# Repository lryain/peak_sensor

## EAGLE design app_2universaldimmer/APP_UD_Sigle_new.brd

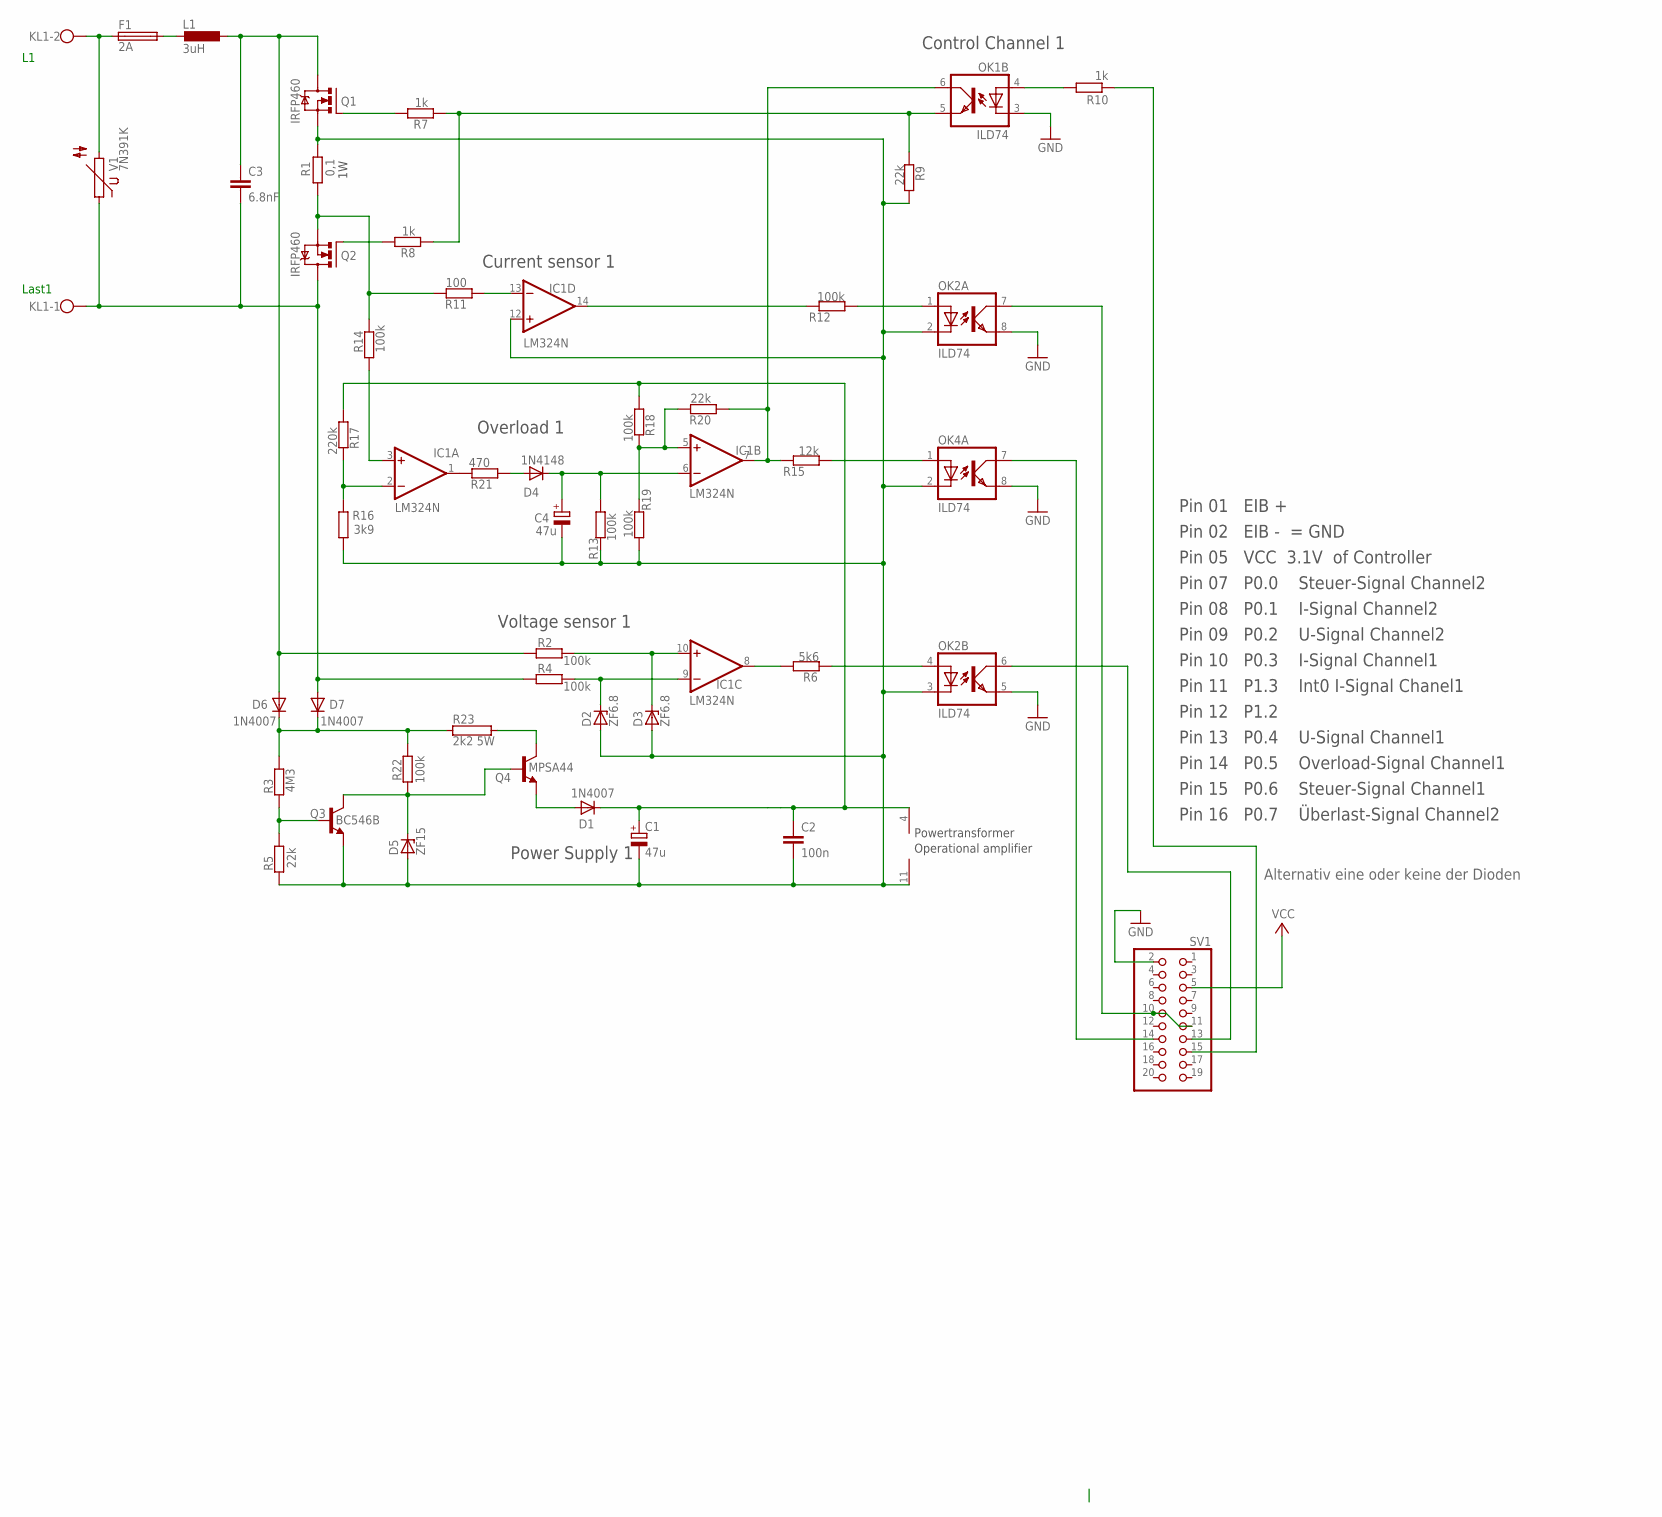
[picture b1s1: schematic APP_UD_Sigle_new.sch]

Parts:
C1, C4: 47u; E2-5
C2: 100n; C025-030X050
C3: 6.8nF; C050-075X075
D1: 1N4007; D-7
D2: ZF6.8; ZDIO-5
D3: ZF6.8; ZDIO-7.5
D4: 1N4148; D-7
D5: ZF15; ZDIO-7.5
D6, D7: 1N4007; D-7.5
F1: 2A; TR5
IC1: LM324N; DIL14
KL1: W237-102
L1: 3uH; 0414V
OK1, OK2, OK4: ILD74; DIL08
Q1, Q2: IRFP460; TO247BV
Q3: BC546B; TO92-EBC
Q4: MPSA44; TO92-EBC
R1: 0,1; 0414V
R2, R4, R12, R13, R14, R18, R19, R22: 100k; 0204/7
R3: 4M3; 0204/7
R5, R9, R20: 22k; 0204/7
R6: 5k6; 0204/7
R7, R8, R10: 1k; 0204/7
R11: 100; 0204/7
R15: 12k; 0204/7
R16: 3k9; 0204/7
R17: 220k; 0204/7
R21: 470; 0204/7
R23: 2k2 5W; KH208-8_10B
SV1: PINHD-2X10; 2X10
V1: 7N391K; S05K11

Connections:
AGND1: C1.-, C2.2, C4.-, D2.A, D3.A, D5.A, IC1.11 (V-), IC1.12 (+IN), OK2.2 (C), OK2.3 (C), OK4.2 (C), Q1.S, Q3.E, R1.2, R5.1, R9.2, R13.2, R16.2, R19.1
GND: OK1.3 (C), OK2.5 (EMIT), OK2.8 (EMIT), OK4.8 (EMIT), SV1.2
unnamed: R10.1, SV1.15
unnamed: OK1.4 (A), R10.2
unnamed: C3.1, D6.A, L1.1, Q1.D, R2.1
unnamed: Q2.S, R1.1, R11.2, R14.2
unnamed: OK2.6 (COL), SV1.13
unnamed: IC1.7 (OUT), OK1.6 (COL), R15.2, R20.1
unnamed: OK2.7 (COL), SV1.10, SV1.11
unnamed: F1.1, KL1.2, V1.2
unnamed: Q2.G, R8.2
unnamed: IC1.3 (+IN), R14.1
unnamed: D6.C, D7.C, R3.2, R22.2, R23.P$1 (1)
unnamed: OK2.4 (A), R6.1
unnamed: IC1.8 (OUT), R6.2
unnamed: Q3.B, R3.1, R5.2
unnamed: Q1.G, R7.2
unnamed: C3.2, D7.A, KL1.1, Q2.D, R4.1, V1.1
unnamed: IC1.2 (-IN), R16.1, R17.2
unnamed: F1.2, L1.2
unnamed: D3.C, IC1.10 (+IN), R2.2
unnamed: D2.C, IC1.9 (-IN), R4.2
unnamed: IC1.1 (OUT), R21.2
unnamed: OK2.1 (A), R12.1
unnamed: C4.+, D4.C, IC1.6 (-IN), R13.1
unnamed: D5.C, Q3.C, Q4.B, R22.1
unnamed: OK4.1 (A), R15.1
unnamed: OK4.7 (COL), SV1.14
unnamed: IC1.5 (+IN), R18.2, R19.2, R20.2
unnamed: Q4.C, R23.P$2 (2)
unnamed: D1.A, Q4.E
unnamed: IC1.14 (OUT), R12.2
unnamed: D4.A, R21.1
unnamed: OK1.5 (EMIT), R7.1, R8.1, R9.1
unnamed: IC1.13 (-IN), R11.1
V12-C1: C1.+, C2.1, D1.C, IC1.4 (V+), R17.1, R18.1
VCC: SV1.5

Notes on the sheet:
Voltage sensor 1
Power Supply 1
Control Channel 1
Pin 05 VCC 3.1V of Controller
Pin 02 EIB - = GND
Pin 01 EIB +
Pin 07 P0.0 Steuer-Signal Channel2
Pin 08 P0.1 I-Signal Channel2
Pin 09 P0.2 U-Signal Channel2
Pin 10 P0.3 I-Signal Channel1
Pin 13 P0.4 U-Signal Channel1
Pin 14 P0.5 Overload-Signal Channel1
Pin 15 P0.6 Steuer-Signal Channel1
Pin 16 P0.7 Überlast-Signal Channel2
Overload 1
Last1
Powertransformer
Operational amplifier
Current sensor 1
Pin 11 P1.3 Int0 I-Signal Chanel1
Pin 12 P1.2
Alternativ eine oder keine der Dioden

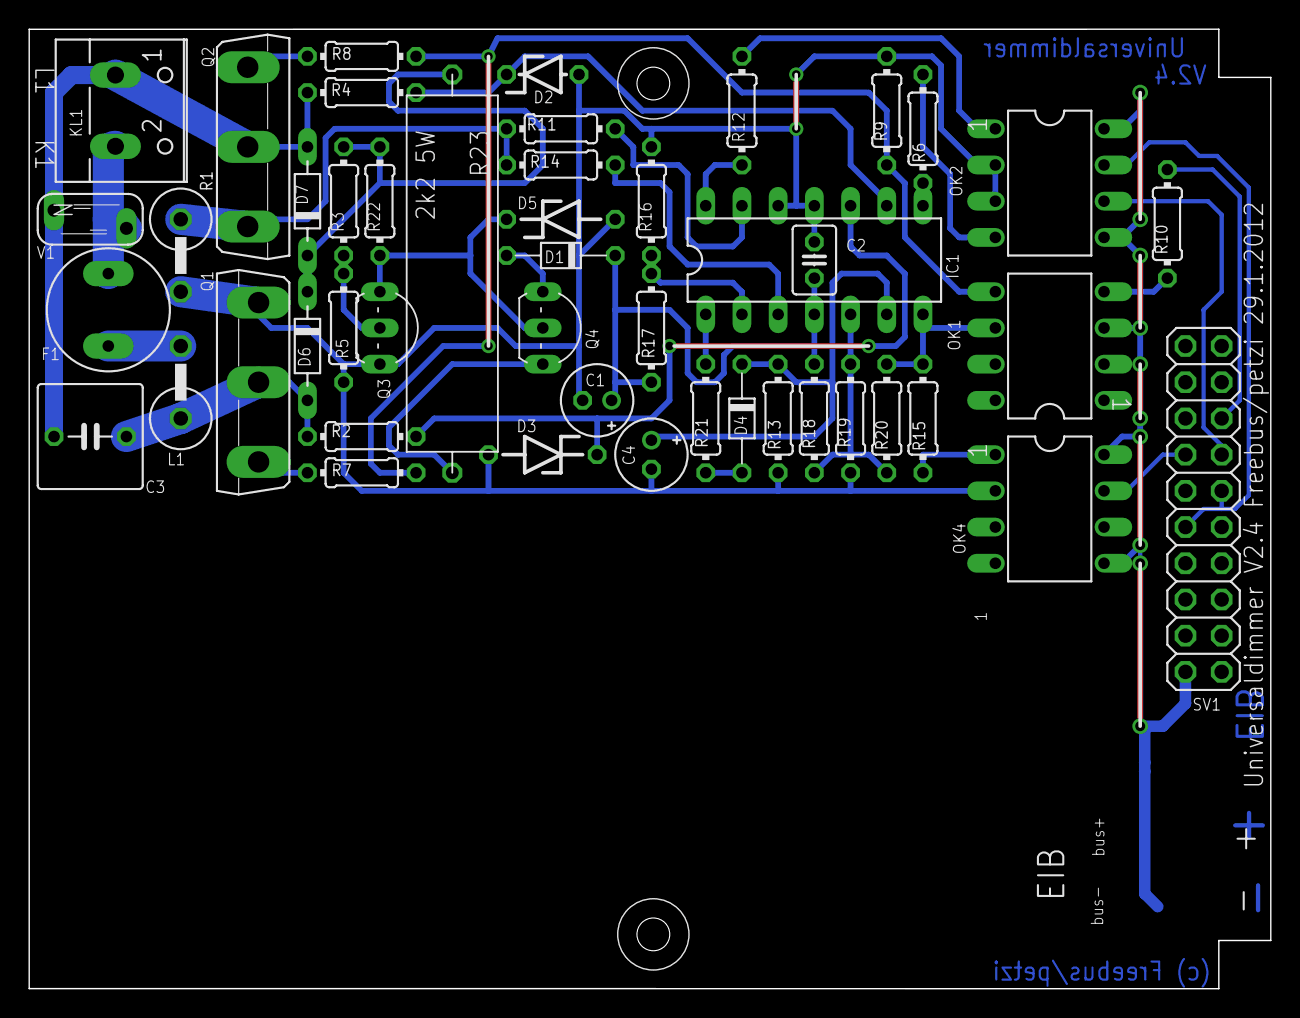
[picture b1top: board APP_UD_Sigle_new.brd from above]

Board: 2 copper layers, 87.1 x 67.3 mm, 47 parts (0 on the bottom side), 36 nets.

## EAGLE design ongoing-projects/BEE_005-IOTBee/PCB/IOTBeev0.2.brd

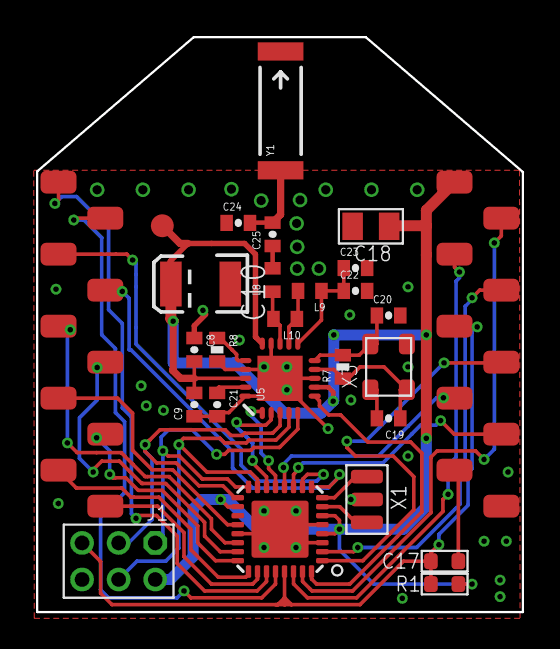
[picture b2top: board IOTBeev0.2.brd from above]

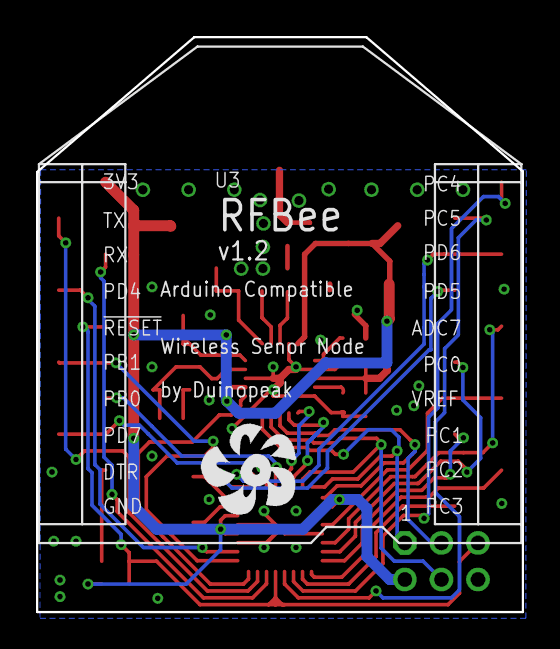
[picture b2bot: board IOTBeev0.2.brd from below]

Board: 2 copper layers, 27.0 x 31.9 mm, 27 parts (2 on the bottom side), 37 nets.

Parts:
C8: 10nF; 0402-CAP
C9: 1nF; 0402-CAP
C10: 10uF; EIA3528
C17: 100nF; 0603_S
C18: 10u; 0805
C19, C20: 22pF; 0402-CAP
C21: 33nF; 0402-CAP
C22: 2.2nF; 0402-CAP
C23: 4.7pF; 0402-CAP
C24: 1.0pF; 0402-CAP
C25: 1.5pF; 0402-CAP
J1: CK_2X3_2.0
L8: 3.9nH; C0402
L9: 2.7nH; C0402
L10: 8.2nH; C0402
R1: 10k; 0603_S
R7: 1M; 0402-RES
R8: 22K; 0402-RES
TP1: PAD.03X.05
U1: MEGA8; MLF32X
U3: 20P-SMD-2.0-BT
U5: NRF24L01ALT1; QFN20_ALT1
U$1: DUINOFUN-LOGO-PCB-0.7
X1: 16MHz; XTAL_3X2
X3: 26MHz; X3225
Y1: ANTENNA2SMD5; ANTENNA-CHIP5

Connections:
!RESET: C17.2, J1.3, R1.2, U1.29, U3.5
+3V3: C8.2, C9.2, C10.A, C18.1, J1.6, R1.1, TP1.P$1, U1.4, U1.6, U1.18, U3.1, U5.7, U5.15, U5.18
ADC7: U1.22, U3.16
ANT: C24.2, C25.2, Y1.FEED
AREF: U1.20, U3.14
CE: U1.13, U5.1
CSN: U1.14, U5.2
DTR: C17.1, U3.9
GND: C8.1, C9.1, C10.C, C18.2, C19.2, C20.2, C21.2, C22.2, C23.2, C24.1, J1.4, R8.2, U1.3, U1.5, U1.21, U1.HEAT, U3.10, U5.0, U5.8, U5.14, U5.17, U5.20, X1.2, X3.1, X3.3
IRQ: U1.32, U5.6
MISO: J1.1, U1.16, U5.5
MOSI: J1.5, U1.15, U5.4
unnamed: U1.7, X1.1
unnamed: U1.8, X1.3
unnamed: C19.1, R7.1, U5.9, X3.2
unnamed: C20.1, R7.2, U5.10, X3.4
unnamed: L8.1, L10.2, U5.13
unnamed: C22.1, C23.1, L9.1, U5.11
unnamed: R8.1, U5.16
unnamed: C21.1, U5.19
unnamed: L9.2, L10.1, U5.12
unnamed: C25.1, L8.2
PB0: U1.12, U3.7
PC0: U1.23, U3.15
PC1: U1.24, U3.13
PC2: U1.25, U3.12
PC3: U1.26, U3.11
PD3: U1.1, U3.6
PD4: U1.2, U3.4
PD5: U1.9, U3.17
PD6: U1.10, U3.18
PD7: U1.11, U3.8
RX: U1.30, U3.3
SCK: J1.2, U1.17, U5.3
SCL: U1.28, U3.19
SDA: U1.27, U3.20
TX: U1.31, U3.2

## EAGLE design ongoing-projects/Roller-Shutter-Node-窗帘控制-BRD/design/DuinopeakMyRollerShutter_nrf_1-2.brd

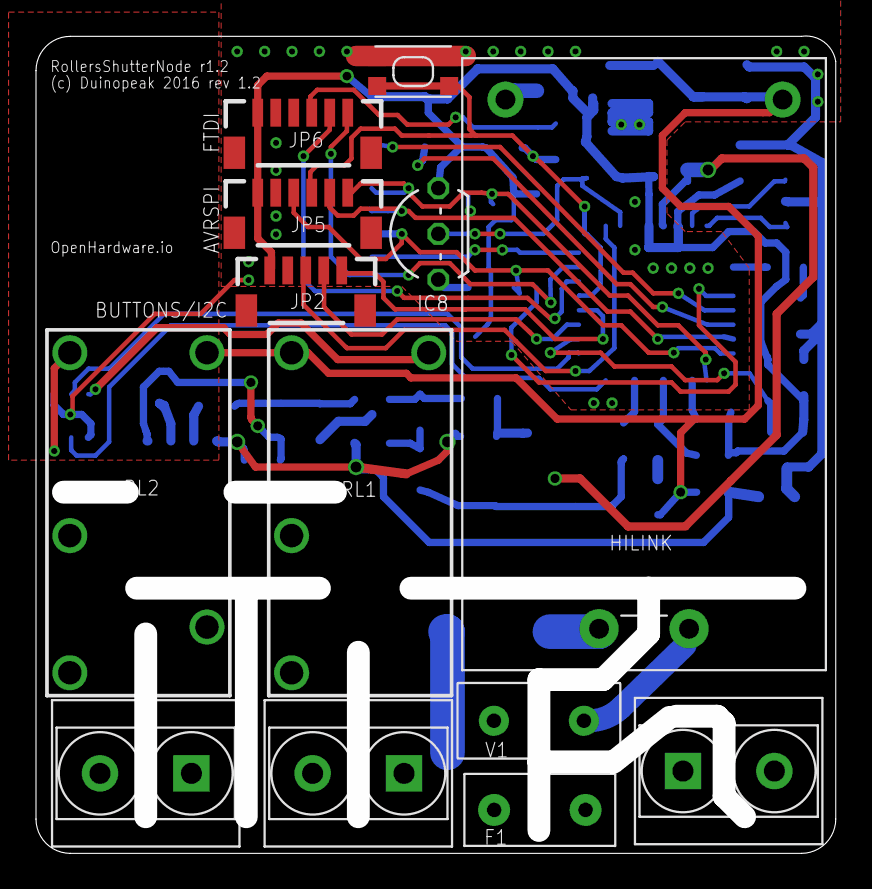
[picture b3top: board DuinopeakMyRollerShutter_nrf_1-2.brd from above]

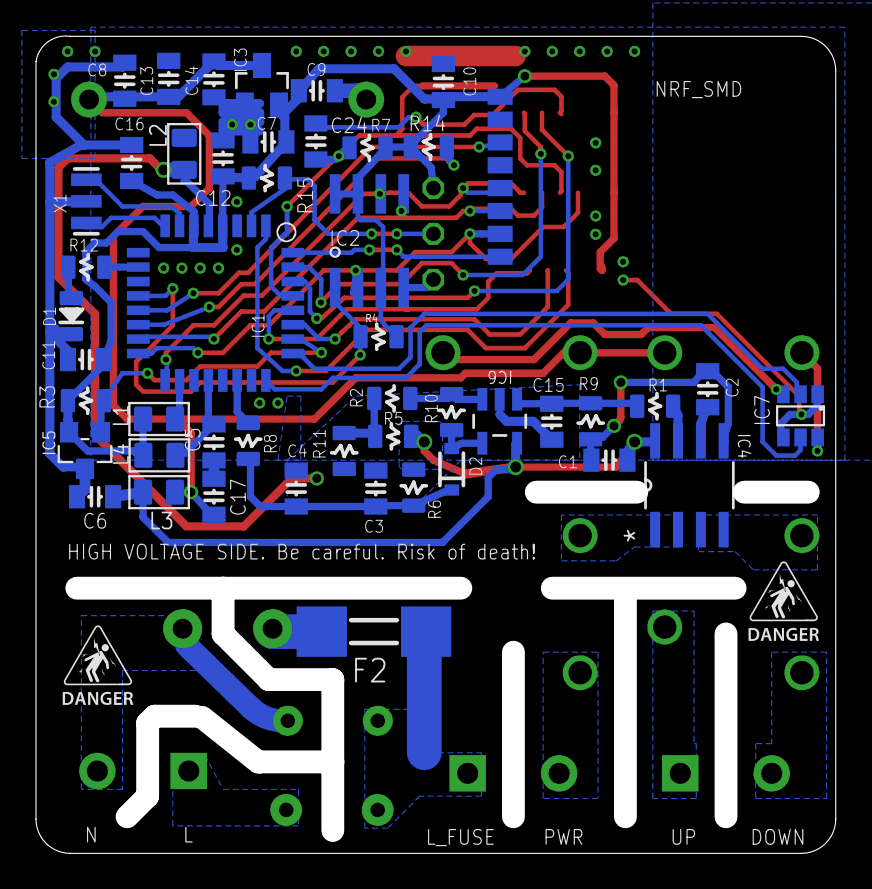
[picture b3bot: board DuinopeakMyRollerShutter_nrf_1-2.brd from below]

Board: 2 copper layers, 44.4 x 45.4 mm, 63 parts (50 on the bottom side), 48 nets.

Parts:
C1: 0.1uf; 0805-CAP
C2, C6, C17: 10n; 0805-CAP
C3, C10, C13: 4u7; 0805-CAP
C4, C5, C7, C11, C12, C14, C16: 0.1u; 0805-CAP
C8: 1u; 0805-CAP
C9: 10u; 0805-CAP
C15: DNP; 0805-CAP
C24: 100n; 0805-CAP
D1: LED0805; 0805-LED
D2: 1n916 type..; SOD-323
F1: FUSE_BEL_RST5_5A
F2: FUSE_MF2410; 2410
HILINK: HILINK_HLK-PM01
IC1: ATMega-328; TQFP32-08
IC2: AT25DF512C-SSHN-B; SO-08
IC3: MCP1703CB; SOT23
IC4: ACS712_5A; SOIC127P600X175-8N
IC5: ATSHA204A; SOT23
IC6: LM321; SOT95P285X120-5N
IC7: MDC3105DMT1
IC8: DS1820; TO92-
J1, J2, J3: SCREW-TERMINAL-2P-3470110P1; 2P-5.0
JP2: 1X05-1MM
JP5, JP6: 1X06-1MM
L1, L2, L3, L4: or 0ohms; L0805
NRF_SMD: NRF24L01+SMD_MODULE
R1, R2, R7, R8, R9, R15: 10k; 0805-RES
R3, R14: 56k; 0805-RES
R4: 0805-RES
R5: 4.7k; 0805-RES
R6: 100k; 0805-RES
R10: 47k; 0805-RES
R11: 2k; 0805-RES
R12: 1k5; 0805-RES
RL1: G5Q-1A-5VDC; G5Q_SINGLE
RL2: G5Q-1-EU-5VDC; RELAY-G5Q
SW1: SPST_TACT-KMR2; KMR2
U$2, U$3: ELECTROCUTION_SMALL
V1: VARISTOR_B72207S251K101
X1: 8 MHz; RESONATOR-SMD

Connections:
5V: C8.1, C13.1, C14.1, C17.1, HILINK.V+, IC3.3, L4.2, RL1.1, RL2.5
12_220: J1.2, RL1.3
A3: IC1.26, IC5.1, R3.1
A4_SDA: IC1.27, JP2.2
A5_SCL: IC1.28, JP2.1
A6_ADC: C3.1, C4.2, D2.1, R6.2, R8.2
A7: IC1.22, R8.1
AGND: C1.2, C2.2, C3.2, C4.1, C15.2, IC1.5, IC4.5, IC6.2, L2.2, R6.1, R9.1, R11.1
AREF: C5.1, IC1.20, L3.1
D0_RX: IC1.30, JP6.5
D1_TX: IC1.31, JP6.6
D2: IC1.32, NRF_SMD.IRQ
D3: IC1.1, JP2.3
D4: IC1.2, IC8.2, R15.2
D9: IC1.13, NRF_SMD.CE
DTR: C24.1, JP6.4
FLASH_CSN: IC1.12, IC2.1, R4.1
GND: C5.2, C6.2, C7.2, C8.2, C9.2, C10.1, C11.2, C12.2, C13.2, C14.2, C16.2, C17.2, D1.MINUS, HILINK.V-, IC1.3, IC1.21, IC2.4, IC3.1, IC5.3, IC7.GND1, IC7.GND2, IC8.1, JP2.4, JP5.2, JP6.2, JP6.3, L2.1, NRF_SMD.GND, SW1.1, SW1.3, X1.2
IN_ACS: IC4.1, IC4.2, RL1.2
L: F1.1, J2.1
LED: IC1.10, R12.1
LM_OUT: D2.2, IC6.4, R10.2
MISO: IC1.16, IC2.2, JP5.3, NRF_SMD.MISO
MOSI: IC1.15, IC2.5, JP5.5, NRF_SMD.MOSI
M_DOWN: J3.2, RL2.3
M_UP: J3.1, RL2.4
N: HILINK.AC2, J2.2, V1.1
unnamed: C2.1, IC4.6
unnamed: IC4.7, R1.1
unnamed: IC1.18, L1.2
unnamed: IC7.VOUT2, RL1.5
unnamed: F2.2, HILINK.AC1
unnamed: C15.1, IC6.1, R1.2, R9.2
unnamed: IC6.3, R2.1, R10.1
unnamed: IC1.7, X1.1
unnamed: D1.PLUS, R12.2
unnamed: R2.2, R5.1, R11.2
unnamed: IC7.VOUT1, RL2.1
unnamed: IC1.8, X1.3
OUT_ACS: IC4.3, IC4.4, RL2.2
PHASE: F1.2, F2.1, J1.1, V1.2
REL_DOWN: IC1.25, IC7.VIN2
REL_UP: IC1.24, IC7.VIN1
RF_CSN: IC1.14, R14.1
RST: C24.2, IC1.29, JP5.4, R7.2, SW1.2, SW1.4
SCK: IC1.17, IC2.6, JP5.6, NRF_SMD.SCK
VCC: C7.1, C9.1, C10.2, C11.1, C12.1, C16.1, IC1.4, IC1.6, IC2.3, IC2.7, IC2.8, IC3.2, IC5.2, IC8.3, JP2.5, JP5.1, JP6.1, L1.1, L3.2, NRF_SMD.3V, R3.2, R4.2, R7.1, R14.2, R15.1
VCC_ACS: C1.1, C6.1, IC4.8, IC6.5, L4.1, R5.2

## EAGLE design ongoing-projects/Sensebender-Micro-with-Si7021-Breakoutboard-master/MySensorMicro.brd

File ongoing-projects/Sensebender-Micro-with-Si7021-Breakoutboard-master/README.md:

# Sensebender-Micro-with-Si7021-Breakoutboard
Clone of the <a href="https://github.com/mysensors/SensebenderMicro">original SenseBender Micro Board</a> but using the Si7021 on a breakout board.

This repository contains a clone of the original Sensebender Micro board from  -> <a href="http://www.mysensors.org">Mysensors</a>

As I find it hard to solder the used Si7021 I decided to exchange it with a breakout variant. Those are available for actually less money than the chip itself on Aliexpress or ebay. Just search for Si7021.

However - as I'm a totally newbie to Eagle, this is a work in progress. So be aware that it is not finished yet and needs some testing. :)

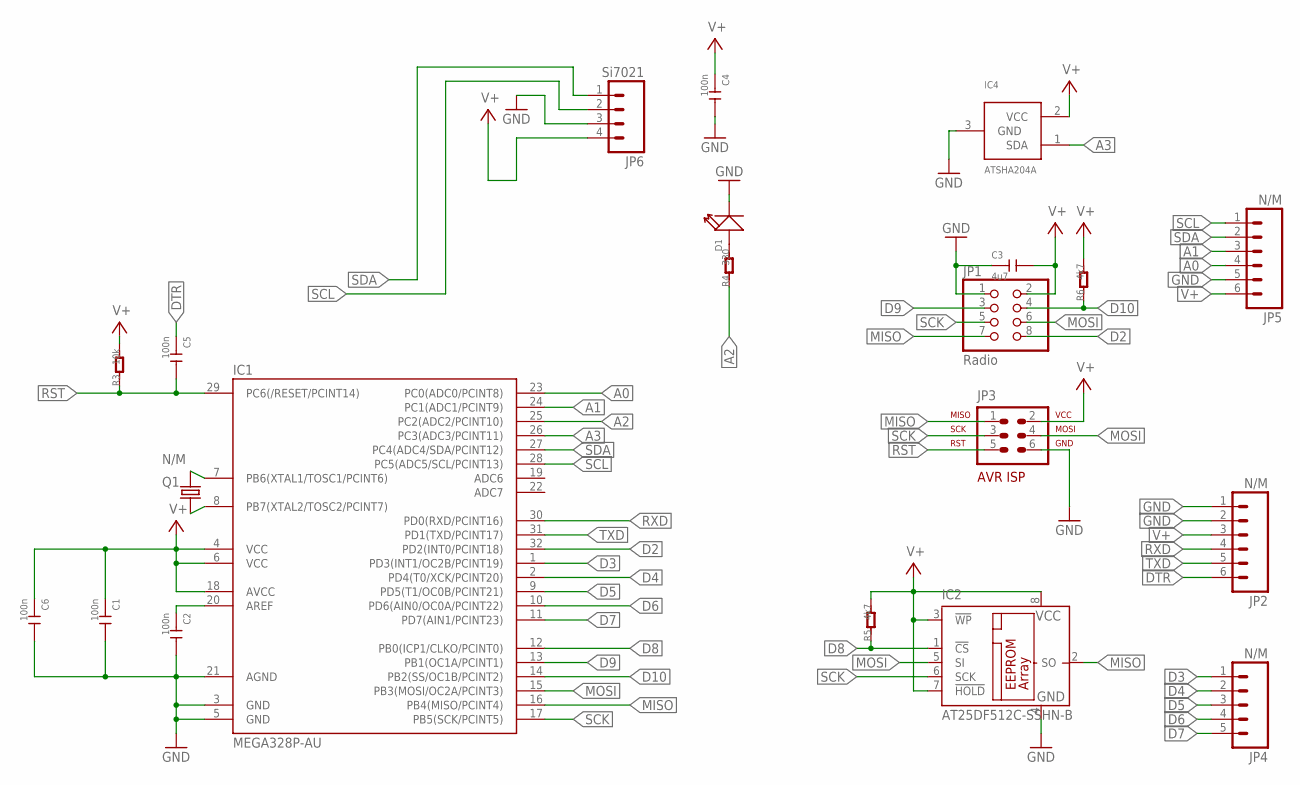
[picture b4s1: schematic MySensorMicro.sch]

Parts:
C1, C2, C4, C5, C6: 100n; C0402
C3: 4u7; C0603
D1: LED-0402
IC1: MEGA328P-AU; TQFP32-08
IC2: AT25DF512C-SSHN-B; SO-08
IC4: ATSHA204A; SOT23
JP1: Radio; 2X04
JP2, JP5: N/M; 1X06_NO_SILK
JP3: N/M; AVR-ISP-6
JP4: N/M; 1X05_NO_SILK
JP6: Si7021; 1X04
Q1: N/M; 2P-L3.2XW1.5MM
R3: 10k; R0402
R4: 330; R0402
R5, R6: 4k7; R0402

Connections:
A0: IC1.23 (PC0(ADC0/PCINT8)), JP5.4
A1: IC1.24 (PC1(ADC1/PCINT9)), JP5.3
A2: IC1.25 (PC2(ADC2/PCINT10)), R4.1
A3: IC1.26 (PC3(ADC3/PCINT11)), IC4.1 (SDA)
D2: IC1.32 (PD2(INT0/PCINT18)), JP1.8
D3: IC1.1 (PD3(INT1/OC2B/PCINT19)), JP4.1
D4: IC1.2 (PD4(T0/XCK/PCINT20)), JP4.2
D5: IC1.9 (PD5(T1/OC0B/PCINT21)), JP4.3
D6: IC1.10 (PD6(AIN0/OC0A/PCINT22)), JP4.4
D7: IC1.11 (PD7(AIN1/PCINT23)), JP4.5
D8: IC1.12 (PB0(ICP1/CLKO/PCINT0)), IC2.1 (!CS), R5.1
D9: IC1.13 (PB1(OC1A/PCINT1)), JP1.3
D10: IC1.14 (PB2(SS/OC1B/PCINT2)), JP1.4, R6.1
DTR: C5.1, JP2.6
GND: C1.2, C2.2, C3.1, C4.2, C6.2, D1.-, IC1.3 (GND), IC1.5 (GND), IC1.21 (AGND), IC2.4 (GND), IC4.3 (GND), JP1.1, JP2.1, JP2.2, JP3.6, JP5.5, JP6.3
MISO: IC1.16 (PB4(MISO/PCINT4)), IC2.2 (SO), JP1.7, JP3.1
MOSI: IC1.15 (PB3(MOSI/OC2A/PCINT3)), IC2.5 (SI), JP1.6, JP3.4
unnamed: IC1.7 (PB6(XTAL1/TOSC1/PCINT6)), Q1.1
unnamed: IC1.8 (PB7(XTAL2/TOSC2/PCINT7)), Q1.2
unnamed: D1.+, R4.2
unnamed: C2.1, IC1.20 (AREF)
RST: C5.2, IC1.29 (PC6(/RESET/PCINT14)), JP3.5, R3.1
RXD: IC1.30 (PD0(RXD/PCINT16)), JP2.4
SCK: IC1.17 (PB5(SCK/PCINT5)), IC2.6 (SCK), JP1.5, JP3.3
SCL: IC1.28 (PC5(ADC5/SCL/PCINT13)), JP5.1, JP6.2
SDA: IC1.27 (PC4(ADC4/SDA/PCINT12)), JP5.2, JP6.1
TXD: IC1.31 (PD1(TXD/PCINT17)), JP2.5
V+: C1.1, C3.2, C4.1, C6.1, IC1.4 (VCC), IC1.6 (VCC), IC1.18 (AVCC), IC2.3 (!WP), IC2.7 (!HOLD), IC2.8 (VCC), IC4.2 (VCC), JP1.2, JP2.3, JP3.2, JP5.6, JP6.4, R3.2, R5.2, R6.2

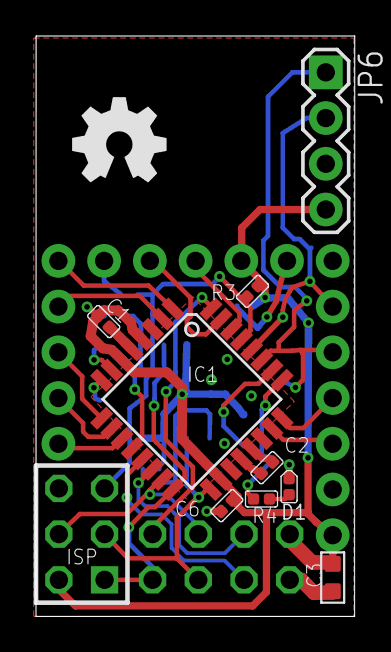
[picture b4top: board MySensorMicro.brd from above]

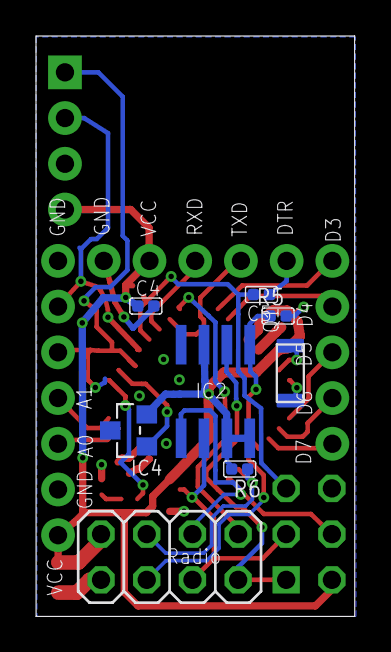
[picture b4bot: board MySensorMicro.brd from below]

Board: 2 copper layers, 17.7 x 32.2 mm, 21 parts (8 on the bottom side), 28 nets.

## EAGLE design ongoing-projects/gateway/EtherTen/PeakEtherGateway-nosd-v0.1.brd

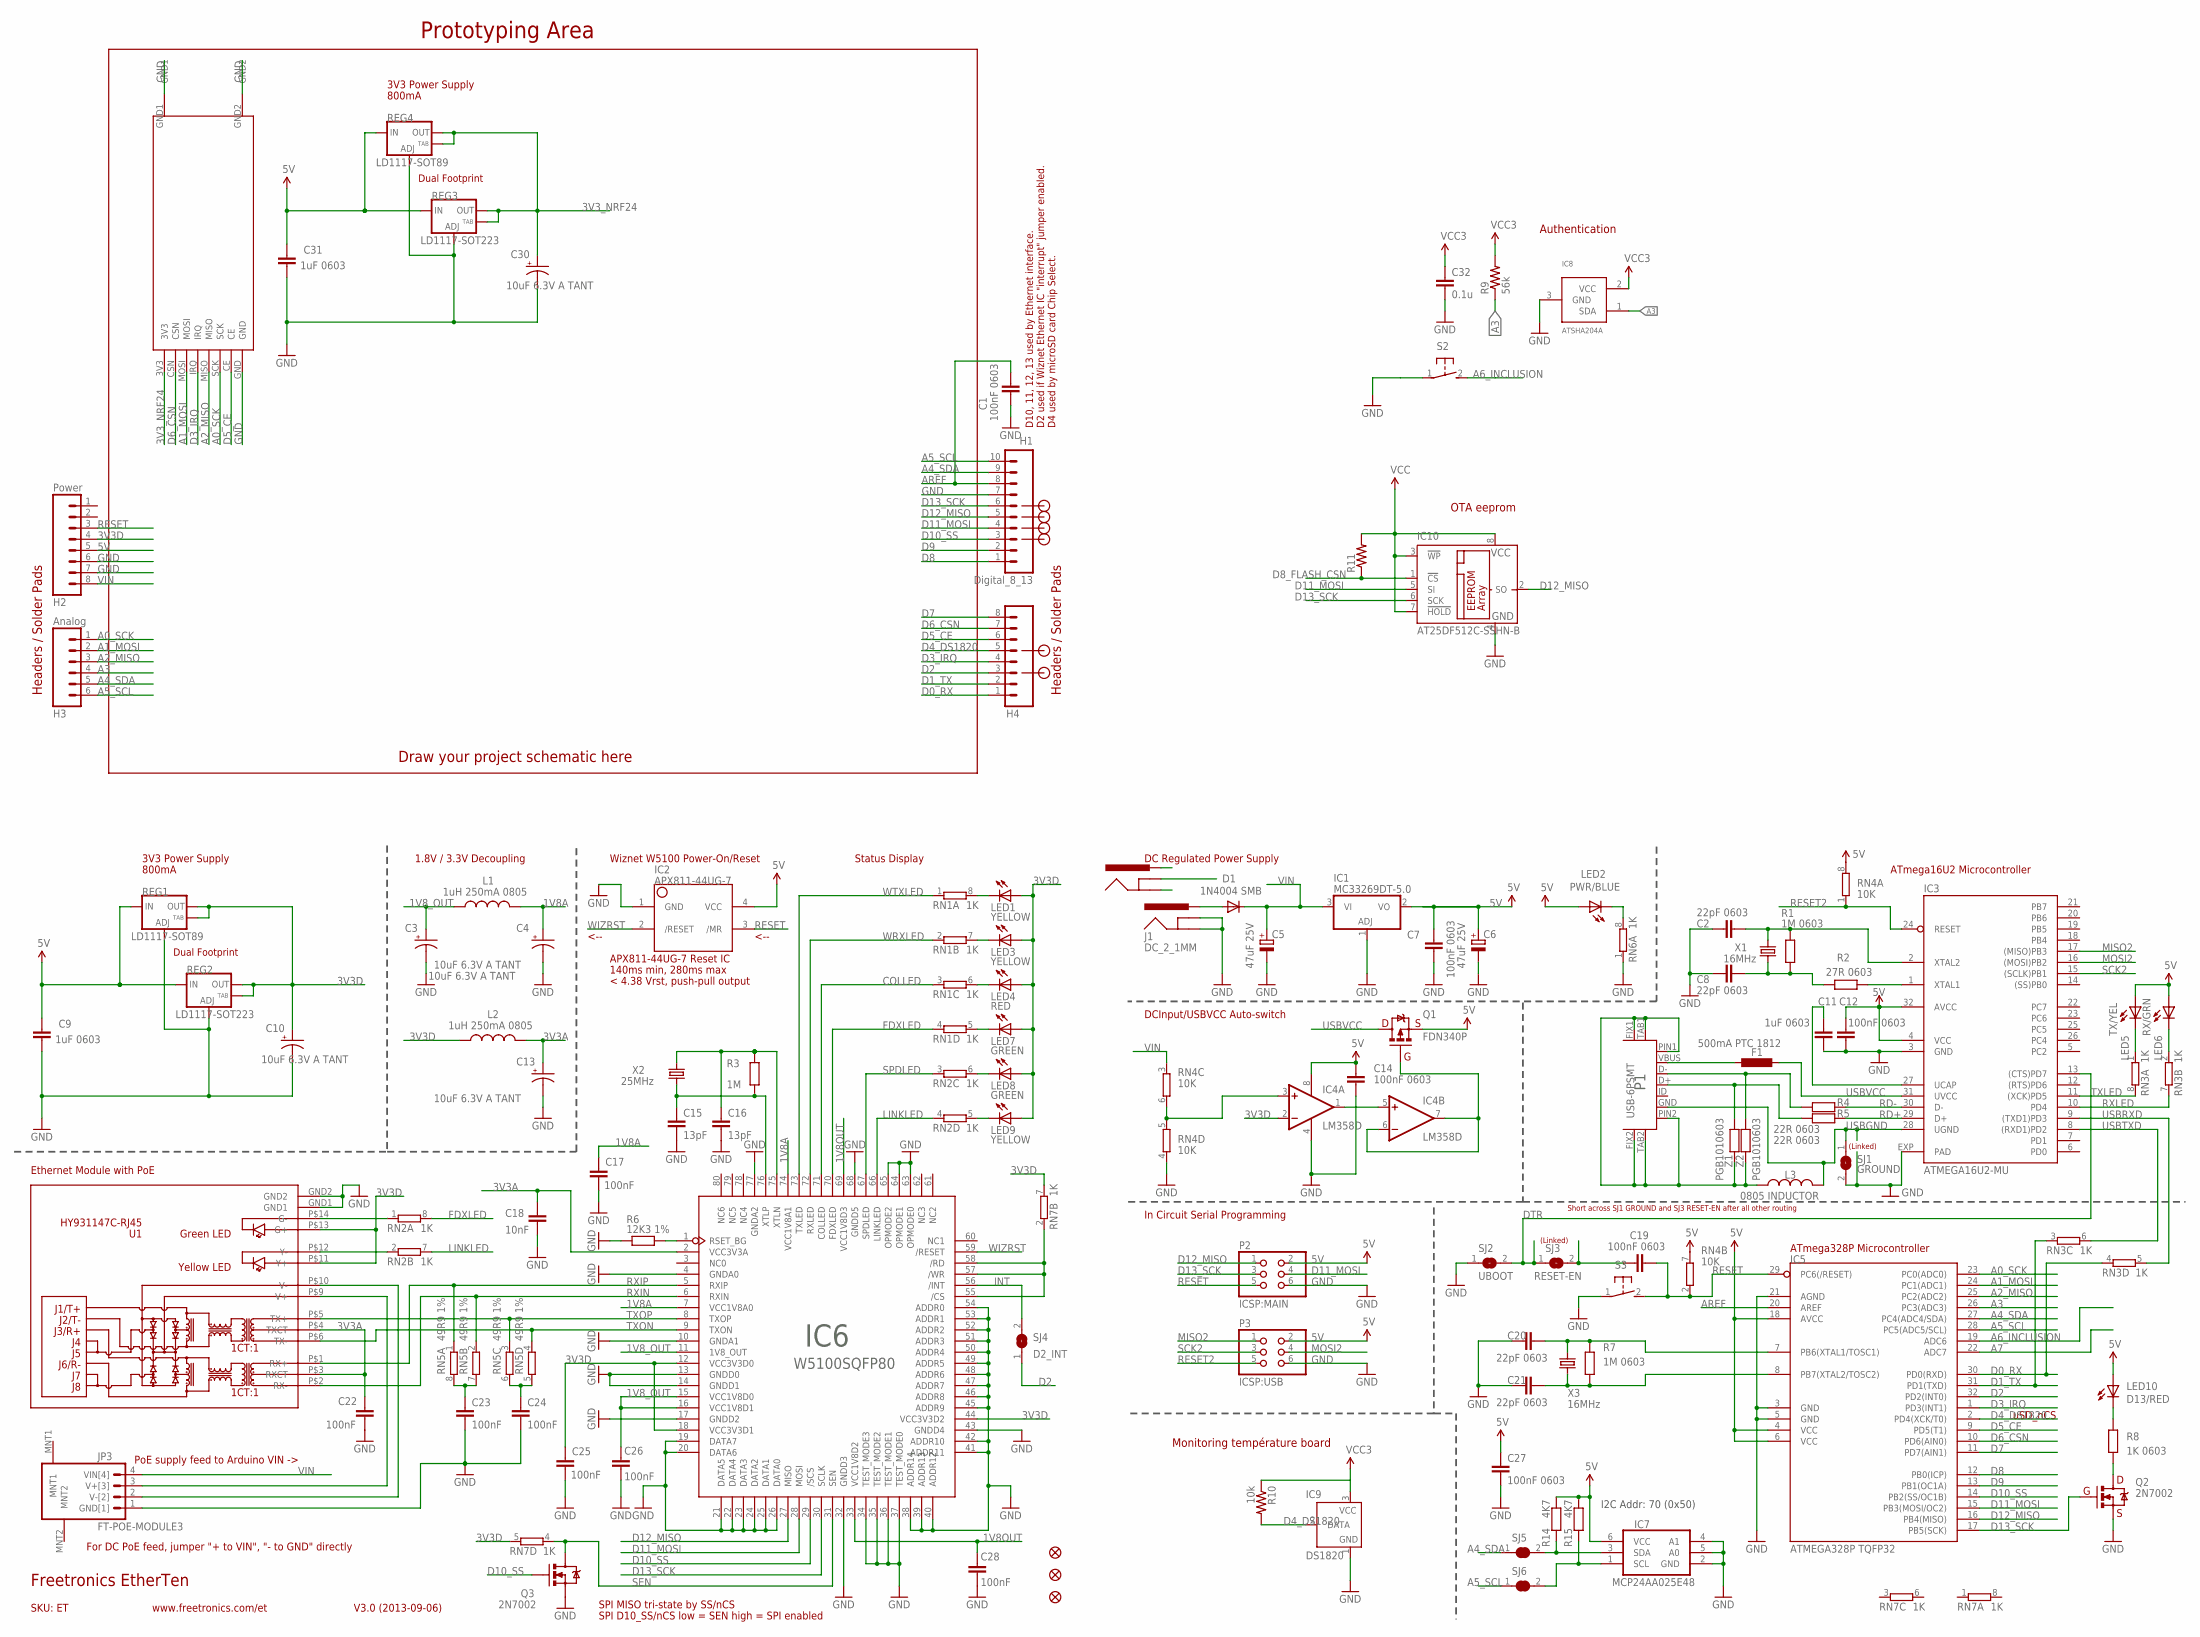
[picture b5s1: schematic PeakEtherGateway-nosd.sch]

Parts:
C1, C7, C12, C14, C19, C27: 100nF 0603; 0603
C2, C8, C20, C21: 22pF 0603; 0603
C3, C4, C10, C13, C30: 10uF 6.3V A TANT; EIA3216
C5, C6: 47uF 25V; PANASONIC_D
C9, C11, C31: 1uF 0603; 0603
C15, C16: 13pF; 0603
C17, C22, C23, C24, C25, C26, C28: 100nF; 0603
C18: 10nF; 0603
C32: 0.1u; 0603-CAP
D1: 1N4004 SMB; SMB-DIODE
F1: 500mA PTC 1812; L1812
FID1, FID2, FID3: FIDUCIAL1X2.5; FIDUCIAL-1X2.5
H1: Digital_8_13; 1X10
H2: Power; 1X08
H3: Analog; 1X06
H4: Digital_0_7; 1X08
IC1: MC33269DT-5.0; DPACK
IC2: APX811-44UG-7; SOT143-R
IC3: ATMEGA16U2-MU; ATMEL_QFN32
IC4: LM358D; SO08
IC5: ATMEGA328P TQFP32; TQFP32-08
IC6: W5100SQFP80; SQFP80
IC7: MCP24AA025E48; SOT23-6
IC8: ATSHA204A; SOT23
IC9: DS1820; TO92-
IC10: AT25DF512C-SSHN-B; SO-08
J1: DC_2_1MM; POWER_JACK_PTH
J2: POWER_JACKOVERPASTE_REDBOARD_0603; POWER_JACK_SMD_OVERPASTE_REDBOARD_0603
JP3: FT-POE-MODULE3; FT-POE-MODULE-NOLABEL
L1, L2: 1uH 250mA 0805; L2012C
L3: 0805 INDUCTOR; 0805-LARGE
LED1, LED3, LED9: YELLOW; LED-0603
LED2: PWR/BLUE; LED-0603
LED4: RED; LED-0603
LED5: TX/YEL; LED-0603
LED6: RX/GRN; LED-0603
LED7, LED8: GREEN; LED-0603
LED10: D13/RED; LED-0603
P1: USB-6PSMT; USB-MICROB-MB05PMXX
P2: ICSP:MAIN; 2X03
P3: ICSP:USB; 2X03
Q1: FDN340P; SOT23
Q2, Q3: 2N7002; SOT23-3
R1, R7: 1M 0603; 0603
R2: 27R 0603; 0603
R3: 1M; 0603
R4, R5: 22R 0603; 0603
R6: 12K3 1%; 0603
R8: 1K 0603; 0603
R9: 56k; 0603-RES
R10: 10k; 0603-RES
R11: RESISTOR0603-RES; 0603-RES
R14, R15: 4K7; 0603
REG1, REG4: LD1117-SOT89; SOT89
REG2, REG3: LD1117-SOT223; SOT223
RN1, RN2, RN3, RN6, RN7: 1K; CAY16
RN4: 10K; CAY16
RN5: 49R9 1%; CAY16
S2, S3: 31-XX; B3F-31XX
SJ1: GROUND; SJ
SJ2: UBOOT; SJ
SJ3: RESET-EN; SJ
SJ4: D2_INT; SJ
SJ5, SJ6: SJCN; SJC
U1: HY931147C-RJ45; HY931147C
U$17: NRF2401; NRF2401_PA_OUTLINE
X1, X3: 16MHz; HC49U-V
X2: 25MHz; HC49U-V
Z1, Z2: PGB1010603; 0603

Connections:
1V8A: C4.A (+), C17.1, IC6.7 (VCC1V8A0), IC6.74 (VCC1V8A1), L1.2
1V8OUT: C28.1, IC6.33 (VCC1V8D2), IC6.69 (VCC1V8D3)
1V8_OUT: C3.A (+), C26.1, IC6.11 (1V8_OUT), IC6.15 (VCC1V8D0), IC6.16 (VCC1V8D1), L1.1
3V3A: C13.A (+), C18.1, C22.1, IC6.2 (VCC3V3A), L2.2, U1.P$3 (RXCT), U1.P$4 (TXCT)
3V3D: C10.A (+), C25.1, H2.4, IC4.2 (-IN), IC6.12 (VCC3V3D0), IC6.18 (VCC3V3D1), IC6.44 (VCC3V3D2), L2.1, LED1.A, LED3.A, LED4.A, LED7.A, LED8.A, LED9.A, REG1.2 (OUT), REG1.4 (OUT), REG2.2 (OUT), REG2.4 (OUT), RN7.5 (2), RN7.7 (2), U1.P$11 (Y+), U1.P$13 (G+)
3V3_NRF24: C30.A (+), C32.1, IC8.2 (VCC), IC9.3 (VCC), IC10.3 (!WP), IC10.7 (!HOLD), IC10.8 (VCC), R9.2, R10.1, R11.2, REG3.2 (OUT), REG3.4 (OUT), REG4.2 (OUT), REG4.4 (OUT), U$17.3V3
5V: C6.+, C7.1, C9.1, C12.1, C14.1, C27.1, C31.1, H2.5, IC1.2 (VO), IC2.4 (VCC), IC3.4 (VCC), IC3.32 (AVCC), IC4.8 (V+), IC5.4 (VCC), IC5.6 (VCC), IC5.18 (AVCC), IC7.6 (VCC), LED2.A, LED5.A, LED6.A, LED10.A, P2.2, P3.2, Q1.2 (S), R14.1, R15.1, REG1.3 (IN), REG2.3 (IN), REG3.3 (IN), REG4.3 (IN), RN4.7 (2), RN4.8 (2)
A0_SCK: H3.1, IC5.23 (PC0(ADC0)), U$17.SCK
A1_MOSI: H3.2, IC5.24 (PC1(ADC1)), U$17.MOSI
A2_MISO: H3.3, IC5.25 (PC2(ADC2)), U$17.MISO
A3: H3.4, IC5.26 (PC3(ADC3)), IC8.1 (SDA), R9.1
A4_SDA: H1.9, H3.5, IC5.27 (PC4(ADC4/SDA)), SJ5.1
A5_SCL: H1.10, H3.6, IC5.28 (PC5(ADC5/SCL)), SJ6.1
A6_INCLUSION: IC5.19 (ADC6), S2.2 (S)
A7: IC5.22 (ADC7); also elsewhere on the board
AREF: C1.1, H1.8, IC5.20 (AREF)
COLLED: IC6.71 (COLLED), RN1.3 (1)
D0_RX: H4.1, IC5.30 (PD0(RXD)), RN3.4 (1)
D1_TX: H4.2, IC5.31 (PD1(TXD)), RN3.3 (1)
D2: H4.3, IC5.32 (PD2(INT0)), SJ4.1
D3_IRQ: H4.4, IC5.1 (PD3(INT1)), U$17.IRQ
D4_DS1820: H4.5, IC5.2 (PD4(XCK/T0)), IC9.2 (DATA), R10.2
D5_CE: H4.6, IC5.9 (PD5(T1)), U$17.CE
D6_CSN: H4.7, IC5.10 (PD6(AIN0)), U$17.CSN
D7: H4.8, IC5.11 (PD7(AIN1))
D8: H1.1, IC5.12 (PB0(ICP))
D8_FLASH_CSN: IC10.1 (!CS), R11.1
D9: H1.2, IC5.13 (PB1(OC1A))
D10_SS: H1.3, IC5.14 (PB2(SS/OC1B)), IC6.29 (/SCS), Q3.1 (G)
D11_MOSI: H1.4, IC5.15 (PB3(MOSI/OC2)), IC6.28 (MOSI), IC10.5 (SI), P2.4
D12_MISO: H1.5, IC5.16 (PB4(MISO)), IC6.27 (MISO), IC10.2 (SO), P2.1
D13_SCK: H1.6, IC5.17 (PB5(SCK)), IC6.30 (SCLK), IC10.6 (SCK), P2.3, Q2.1 (G)
DTR: IC3.13 ((CTS)PD7), SJ2.2, SJ3.1
FDXLED: IC6.70 (FDXLED), RN1.4 (1), RN2.8 (2)
GND: C1.2, C2.1, C3.C (-), C4.C (-), C5.-, C6.-, C7.2, C8.1, C9.2, C10.C (-), C11.2, C12.2, C13.C (-), C14.2, C15.2, C16.2, C17.2, C18.2, C20.1, C21.1, C22.2, C23.2, C24.2, C25.2, C26.2, C27.2, C28.2, C30.C (-), C31.2, C32.2, H1.7, H2.6, H2.7, IC1.1 (ADJ), IC2.1 (GND), IC3.3 (GND), IC3.EXP (PAD), IC4.4 (V-), IC5.3 (GND), IC5.5 (GND), IC5.21 (AGND), IC6.4 (GNDA0), IC6.10 (GNDA1), IC6.13 (GNDD0), IC6.14 (GNDD1), IC6.17 (GNDD2), IC6.19 (DATA7), IC6.20 (DATA6), IC6.21 (DATA5), IC6.22 (DATA4), IC6.23 (DATA3), IC6.24 (DATA2), IC6.25 (DATA1), IC6.26 (DATA0), IC6.32 (GNDD3), IC6.34 (TEST_MODE3), IC6.35 (TEST_MODE2), IC6.36 (TEST_MODE1), IC6.37 (TEST_MODE0), IC6.38 (ADDR14), IC6.39 (ADDR13), IC6.40 (ADDR12), IC6.41 (ADDR11), IC6.42 (ADDR10), IC6.43 (GNDD4), IC6.45 (ADDR9), IC6.46 (ADDR8), IC6.47 (ADDR7), IC6.48 (ADDR6), IC6.49 (ADDR5), IC6.50 (ADDR4), IC6.51 (ADDR3), IC6.52 (ADDR2), IC6.53 (ADDR1), IC6.54 (ADDR0), IC6.63 (OPMODE0), IC6.64 (OPMODE1), IC6.65 (OPMODE2), IC6.68 (GNDD5), IC6.77 (GNDA2), IC7.2 (GND), IC7.4 (A1), IC7.5 (A0), IC8.3 (GND), IC9.1 (GND), IC10.4 (GND), J1.GND, J1.GNDBREAK, JP3.1 (GND[1]), P2.6, P3.6, Q2.2 (S), Q3.2 (S), R6.1, REG1.1 (ADJ), REG2.1 (ADJ), REG3.1 (ADJ), REG4.1 (ADJ), RN4.4 (1), RN6.1, S2.1, S3.1, SJ1.2, SJ2.1, U1.GND1, U1.GND2, U$17.GND
INT: IC6.56 (/INT), SJ4.2
LINKLED: IC6.66 (LINKLED), RN2.4 (1), RN2.7 (2)
MISO2: IC3.17 ((MISO)PB3), P3.1
MOSI2: IC3.16 ((MOSI)PB2), P3.4
unnamed: C24.1, RN5.5 (2), RN5.6 (2)
unnamed: C20.2, IC5.7 (PB6(XTAL1/TOSC1)), R7.2, X3.2
unnamed: C19.1, SJ3.2
unnamed: LED10.C, R8.2
unnamed: IC7.1 (SCL), R15.2, SJ6.2
unnamed: Q2.3 (D), R8.1
unnamed: C21.2, IC5.8 (PB7(XTAL2/TOSC2)), R7.1, X3.1
unnamed: IC3.1 (XTAL1), R2.1
unnamed: L3.1, P1.FIX1, P1.FIX2, P1.PIN1, P1.PIN2, P1.TAB1, P1.TAB2, Z1.2, Z2.2
unnamed: LED6.C, RN3.2 (1)
unnamed: IC4.3 (+IN), RN4.5 (2), RN4.6 (2)
unnamed: LED5.C, RN3.1
unnamed: LED2.C, RN6.8 (2)
unnamed: P1.D+, R5.2, Z1.1
unnamed: P1.D-, R4.2, Z2.1
unnamed: IC4.6 (-IN), IC4.7 (OUT), Q1.1 (G)
unnamed: IC4.1 (OUT), IC4.5 (+IN)
unnamed: LED8.C, RN2.6 (2)
unnamed: IC6.55 (/CS), IC6.57 (/WR), IC6.58 (/RD), RN7.2 (1)
unnamed: LED9.C, RN2.5 (2)
unnamed: IC7.3 (SDA), R14.2, SJ5.2
unnamed: D1.A, J1.PWR
unnamed: RN2.1, U1.P$14 (G-)
unnamed: JP3.3 (V+[3]), U1.P$9 (V+)
unnamed: JP3.2 (V-[2]), U1.P$10 (V-)
unnamed: C2.2, IC3.2 (XTAL2), R1.2, X1.2
unnamed: C8.2, R1.1, R2.2, X1.1
unnamed: F1.1, P1.VBUS
unnamed: C11.1, IC3.27 (UCAP)
unnamed: C23.1, RN5.7 (2), RN5.8 (2)
unnamed: IC6.1 (RSET_BG), R6.2
unnamed: LED7.C, RN1.5 (2)
unnamed: LED4.C, RN1.6 (2)
unnamed: LED3.C, RN1.7 (2)
unnamed: LED1.C, RN1.8 (2)
unnamed: RN2.2 (1), U1.P$12 (Y-)
RD+: IC3.29 (D+), R5.1
RD-: IC3.30 (D-), R4.1
RESET: C19.2, H2.3, IC2.3 (/MR), IC5.29 (PC6(/RESET)), P2.5, RN4.2 (1), S3.2 (S)
RESET2: IC3.24 (RESET), P3.5, RN4.1
RXIN: IC6.6 (RXIN), RN5.2 (1), U1.P$2 (RX-)
RXIP: IC6.5 (RXIP), RN5.1, U1.P$1 (RX+)
RXLED: IC3.10 (PD4), RN3.7 (2)
SCK2: IC3.15 ((SCLK)PB1), P3.3
SEN: IC6.31 (SEN), Q3.3 (D), RN7.4 (1)
SPDLED: IC6.67 (SPDLED), RN2.3 (1)
TXLED: IC3.11 ((XCK)PD5), RN3.8 (2)
TXON: IC6.9 (TXON), RN5.4 (1), U1.P$6 (TX-)
TXOP: IC6.8 (TXOP), RN5.3 (1), U1.P$5 (TX+)
USBGND: IC3.28 (UGND), L3.2, P1.GND, SJ1.1
USBRXD: IC3.9 ((TXD1)PD3), RN3.5 (2)
USBTXD: IC3.8 ((RXD1)PD2), RN3.6 (2)
USBVCC: F1.2, IC3.31 (UVCC), Q1.3 (D)
VIN: C5.+, D1.C, H2.8, IC1.3 (VI), JP3.4 (VIN[4]), RN4.3 (1)
WIZRST: IC2.2 (/RESET), IC6.59 (/RESET)
WRXLED: IC6.72 (RXLED), RN1.2 (1)
WTXLED: IC6.73 (TXLED), RN1.1
XTLN: C16.1, IC6.75 (XTLN), R3.2, X2.2
XTLP: C15.1, IC6.76 (XTLP), R3.1, X2.1

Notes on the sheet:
Prototyping Area
SKU: ET
3V3 Power Supply
Status Display
Headers / Solder Pads
Dual Footprint
1.8V / 3.3V Decoupling
Draw your project schematic here
D10, 11, 12, 13 used by Ethernet interface.
D2 used if Wiznet Ethernet IC "interrupt" jumper enabled.
PoE supply feed to Arduino VIN ->
SPI MISO tri-state by SS/nCS
SPI D10_SS/nCS low = SEN high = SPI enabled
For DC PoE feed, jumper "+ to VIN", "- to GND" directly
DC Regulated Power Supply
ATmega328P Microcontroller
APX811-44UG-7 Reset IC
140ms min, 280ms max
ATmega16U2 Microcontroller
DCInput/USBVCC Auto-switch
Wiznet W5100 Power-On/Reset
uSD_nCS
800mA
In Circuit Serial Programming
Freetronics EtherTen
V3.0 (2013-09-06)
www.freetronics.com/et
Ethernet Module with PoE
< 4.38 Vrst, push-pull output
<--
D4 used by microSD card Chip Select.
(Linked)
Short across SJ1 GROUND and SJ3 RESET-EN after all other routing
I2C Addr: 70 (0x50)
Authentication
Monitoring température board
OTA eeprom

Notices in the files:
app_2universaldimmer/APP_UD_Sigle_new.sch:
COPYRIGHT: (c) R. Petzoldt
parts and their libraries:
SparkFun-DiscreteSemi: Licensing: Creative Commons ShareAlike 4.0 International - https://creativecommons.org/licenses/by-sa/4.0
freetronics-original: Licensing: CC v3.0 Share-Alike You are welcome to use this library for commercial purposes.
